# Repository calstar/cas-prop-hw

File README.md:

View this project on [CADLAB.io](https://cadlab.io/project/23051).

# cas-prop-hw
Common Avionics Stack - Prop Module - Hardware

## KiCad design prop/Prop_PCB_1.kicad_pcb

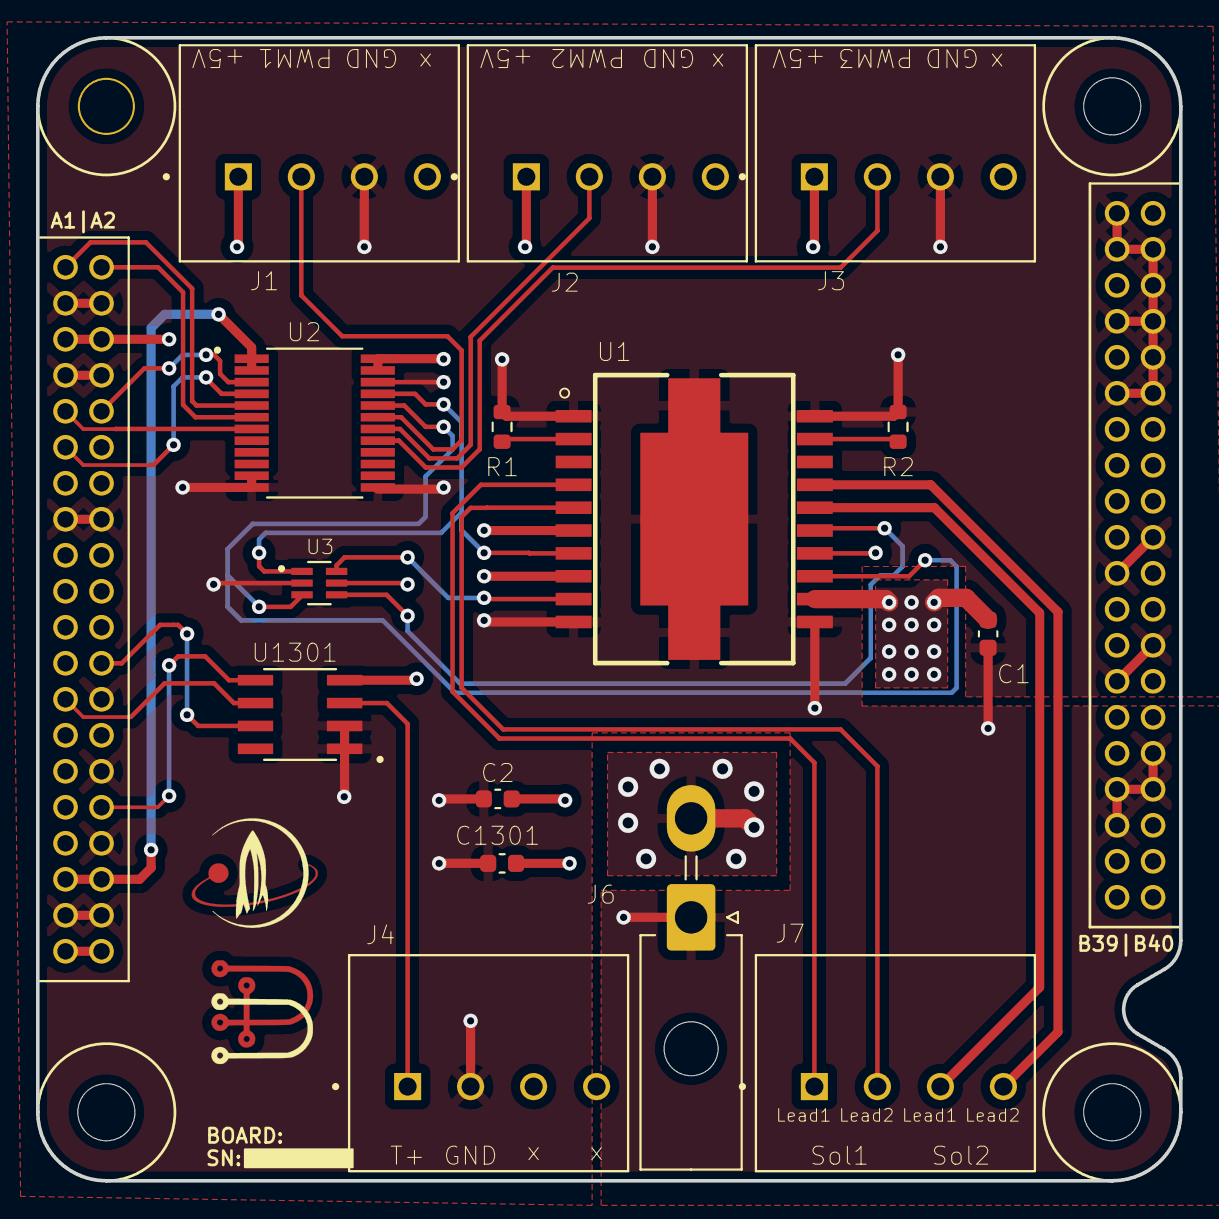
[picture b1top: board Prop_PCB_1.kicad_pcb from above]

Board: 4 copper layers, 63.5 x 63.5 mm, 18 parts (0 on the bottom side), 27 nets.

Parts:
C1, C2: 100n; C_0603_1608Metric
C1301: 0.1u; C_0603_1608Metric
J1, J2, J3, J4, J7: 1984989; PHOENIX_1984989
J5: CAS_stacking; CAS_physical
J6: Conn_01x02; Molex_Mini-Fit_Jr_5569-02A2_2x01_P4.20mm_Horizontal
R1, R2: 20; R_0603_1608Metric
Ref**: Val**; star_fancy
Ref**#2: Val**; bac
U1: L298P; SOIC127P1420X360-20N
U2: SN74LVC8T245DBR; SN74LVC8T245DBR_SOP65P780X200-24N
U3: SN74LVC2GU04DCKR; SN74LVC2GU04_SOT65P210X110-6N
U1301: MAX6675ISA+; SOIC127P600X175-8N

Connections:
+3V3: J5.A35 (3.3VA), J5.A36 (3.3VB), U2.1 (VCCA), U2.2 (DIR)
+5V: C2.2, C1301.1, J1.1, J2.1, J3.1, J5.A5 (5VA), J5.A6 (5VB), U1.6 (Vs), U1.8 (EnA), U1.14 (EnB), U2.23 (VCCB), U2.24 (VCCB), U3.5 (VCC), U1301.4 (VCC)
+24V: C1.1, J6.2, U1.12 (Vss)
+BATT: J5.A39 (VDD_BATTA), J5.A40 (VDD_BATTB)
/MAX6675ISA/T+: J4.1, U1301.3 (T+)
CS4: J5.A25 (SPI0_nSS4), U1301.6 (~CS)
GND: C1.2, C2.1, C1301.2, J1.3, J2.3, J3.3, J4.2, J5.A3 (GND1), J5.A4 (GND2), J5.A7 (GND3), J5.A8 (GND4), J5.A15 (GND5), J5.A16 (GND6), J5.A26 (GND7), J5.A30 (GND8), J5.A34 (GND9), J5.A37 (GND10), J5.A38 (GND11), J5.B1 (GND12), J5.B3 (GND13), J5.B4 (GND14), J5.B6 (GND15), J5.B7 (GND16), J5.B8 (GND17), J5.B10 (GND18), J5.B11 (GND19), J5.B12 (GND20), J5.B20 (GND22), J5.B21 (GND23), J5.B26 (GND24), J5.B27 (GND25), J5.B32 (GND26), J5.B33 (GND27), J5.B34 (GND28), J5.B35 (GND29), J6.1, R1.1, R2.2, U1.1 (GND), U1.10 (GND), U1.11 (GND), U1.20 (GND), U1.21, U1.22, U1.23, U2.11 (GND), U2.12 (GND), U2.13 (GND), U2.22 (OE), U3.2 (GND), U1301.1 (GND), U1301.2 (T-)
unnamed: R1.2, U1.2 (SENSE_A)
unnamed: R2.1, U1.19 (SENSE_B)
PWM1: J1.2, U2.19 (B3)
PWM1_33: J5.A1 (INT1), U2.5 (A3)
PWM2: J2.2, U2.18 (B4)
PWM2_33: J5.A2 (INT2), U2.6 (A4)
PWM3: J3.2, U2.17 (B5)
PWM3_33: J5.A9 (INT3), U2.7 (A5)
SPI0_MISO: J5.A24 (SPI0_MISO), U1301.7 (SO)
SPI0_SCK: J5.A32 (SPI0_SCK), U1301.5 (SCK)
Sol1: U1.7 (IN1), U2.21 (B1), U3.1 (1A)
Sol1': U1.9 (IN2), U3.6 (1Y)
Sol1Lead1: J7.1, U1.4 (OUT1)
Sol1Lead2: J7.2, U1.5 (OUT2)
Sol1_33: J5.A10 (INT4), U2.3 (A1)
Sol2: U1.13 (IN3), U2.20 (B2), U3.3 (2A)
Sol2': U1.15 (IN4), U3.4 (2Y)
Sol2Lead1: J7.3, U1.16 (OUT3)
Sol2Lead2: J7.4, U1.17 (OUT4)
Sol2_33: J5.A11 (INT5), U2.4 (A2)

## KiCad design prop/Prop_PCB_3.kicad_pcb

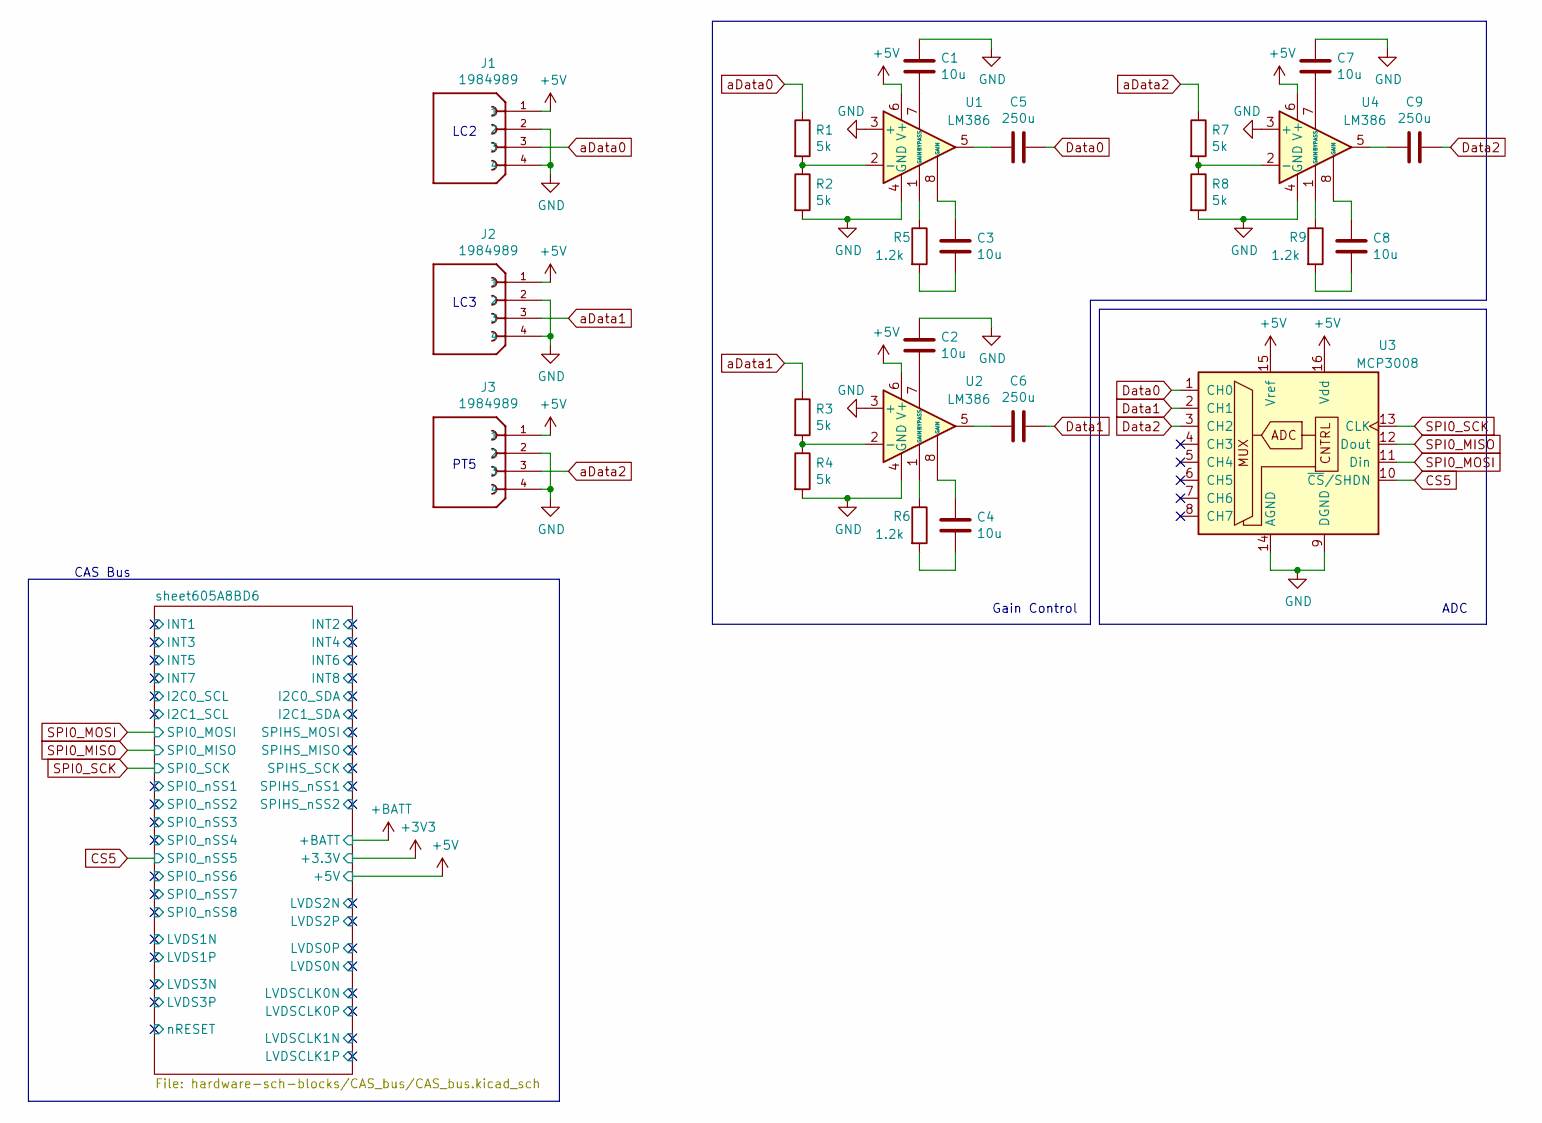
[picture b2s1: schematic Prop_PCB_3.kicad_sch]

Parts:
C1, C2, C3, C4, C7, C8: 10u; C_0603_1608Metric
C5, C6, C9: 250u; C_0603_1608Metric
J1, J2, J3: 1984989; PHOENIX_1984989; PARTREV 2018-11-03
R1, R2, R3, R4, R7, R8: 5k; R_0603_1608Metric
R5, R6, R9: 1.2k; R_0603_1608Metric
U1, U2, U4: LM386; SOIC-8_3.9x4.9mm_P1.27mm
U3: MCP3008; SOIC-16_3.9x9.9mm_P1.27mm

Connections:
+5V: J1.1, J2.1, J3.1, U1.6 (V+), U2.6 (V+), U3.15 (Vref), U3.16 (Vdd), U4.6 (V+); also elsewhere on the board
CS5: U3.10 (~CS/SHDN); also elsewhere on the board
Data0: C5.1, U3.1 (CH0)
Data1: C6.1, U3.2 (CH1)
Data2: C9.1, U3.3 (CH2)
GND: C1.1, C2.1, C7.1, J1.2, J1.4, J2.2, J2.4, J3.2, J3.4, R2.2, R4.2, R8.2, U1.3 (+), U1.4 (GND), U2.3 (+), U2.4 (GND), U3.9 (DGND), U3.14 (AGND), U4.3 (+), U4.4 (GND); also elsewhere on the board
unnamed: C1.2, U1.7 (BYPASS)
unnamed: C2.2, U2.7 (BYPASS)
unnamed: C3.1, U1.8 (GAIN)
unnamed: C3.2, R5.2
unnamed: C4.1, U2.8 (GAIN)
unnamed: C4.2, R6.2
unnamed: C5.2, U1.5
unnamed: C6.2, U2.5
unnamed: C7.2, U4.7 (BYPASS)
unnamed: C8.1, U4.8 (GAIN)
unnamed: C8.2, R9.2
unnamed: C9.2, U4.5
unnamed: R1.2, R2.1, U1.2 (-)
unnamed: R3.2, R4.1, U2.2 (-)
unnamed: R5.1, U1.1 (GAIN)
unnamed: R6.1, U2.1 (GAIN)
unnamed: R7.2, R8.1, U4.2 (-)
unnamed: R9.1, U4.1 (GAIN)
SPI0_MISO: U3.12 (Dout); also elsewhere on the board
SPI0_MOSI: U3.11 (Din); also elsewhere on the board
SPI0_SCK: U3.13 (CLK); also elsewhere on the board
aData0: J1.3, R1.1
aData1: J2.3, R3.1
aData2: J3.3, R7.1

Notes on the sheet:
CAS Bus
LC2
Gain Control
ADC
PT5
LC3

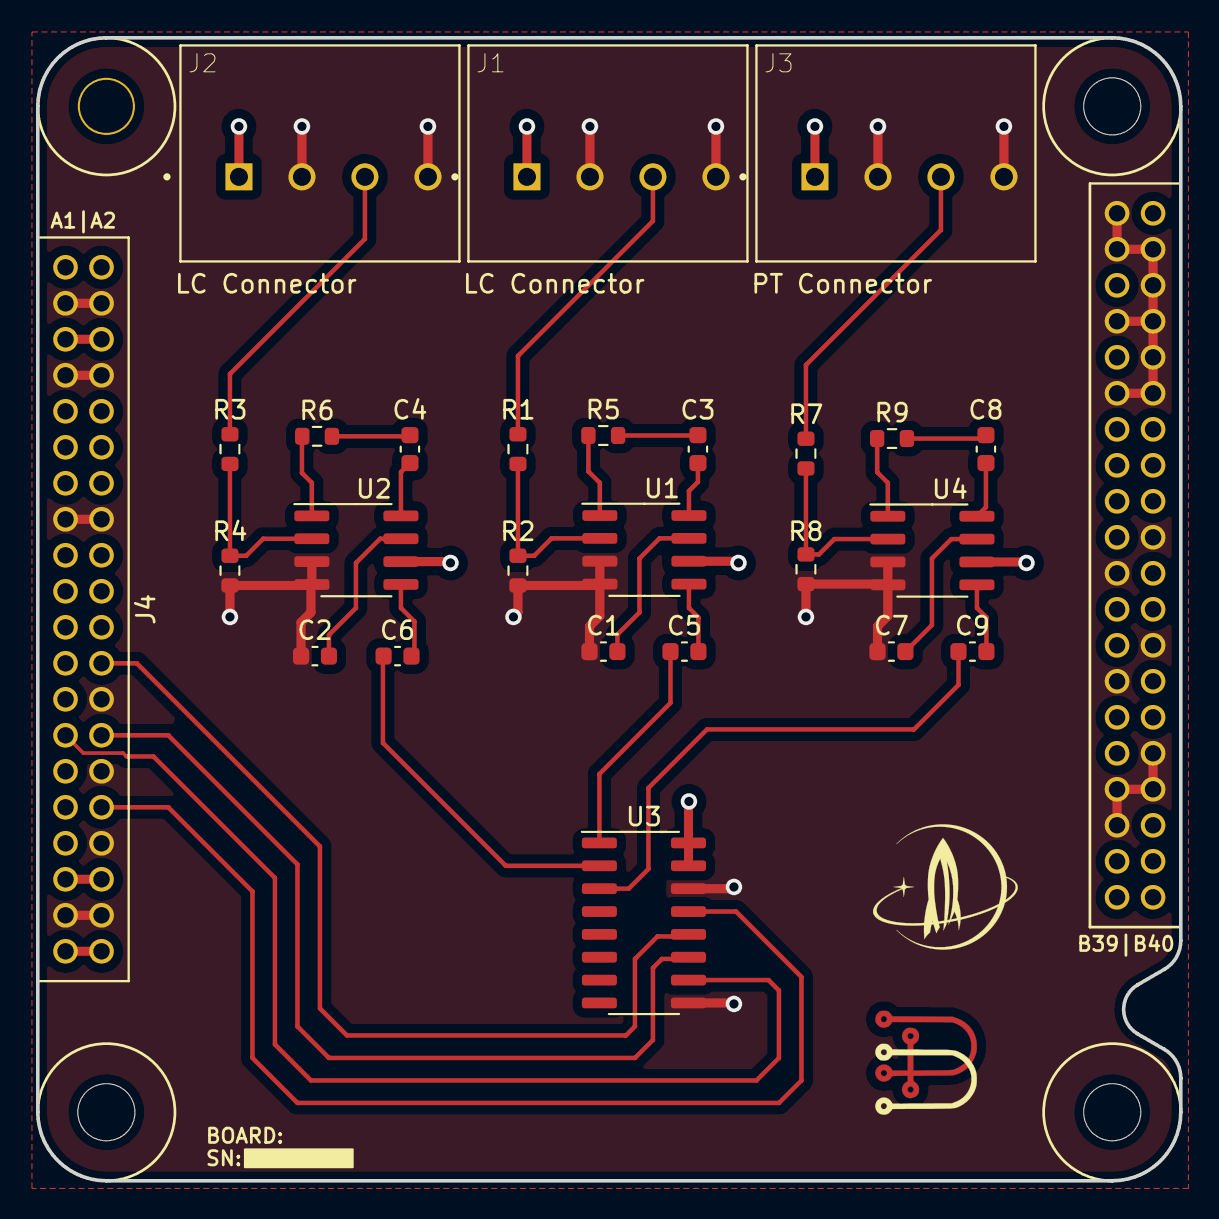
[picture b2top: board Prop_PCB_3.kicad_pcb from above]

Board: 4 copper layers, 63.5 x 63.5 mm, 27 parts (0 on the bottom side), 32 nets.

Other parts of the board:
J4: CAS_stacking; CAS_physical
Ref**: Val**; bac

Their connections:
+3V3: J4.A35 (3.3VA), J4.A36 (3.3VB)
+5V: J4.A5 (5VA), J4.A6 (5VB); also elsewhere on the board
+BATT: J4.A39 (VDD_BATTA), J4.A40 (VDD_BATTB)
CS5: J4.A27 (SPI0_nSS5); also elsewhere on the board
GND: J4.A3 (GND1), J4.A4 (GND2), J4.A7 (GND3), J4.A8 (GND4), J4.A15 (GND5), J4.A16 (GND6), J4.A26 (GND7), J4.A30 (GND8), J4.A34 (GND9), J4.A37 (GND10), J4.A38 (GND11), J4.B1 (GND12), J4.B3 (GND13), J4.B4 (GND14), J4.B6 (GND15), J4.B7 (GND16), J4.B8 (GND17), J4.B10 (GND18), J4.B11 (GND19), J4.B12 (GND20), J4.B20 (GND22), J4.B21 (GND23), J4.B26 (GND24), J4.B27 (GND25), J4.B32 (GND26), J4.B33 (GND27), J4.B34 (GND28), J4.B35 (GND29); also elsewhere on the board
SPI0_MISO: J4.A24 (SPI0_MISO); also elsewhere on the board
SPI0_MOSI: J4.A28 (SPI0_MOSI); also elsewhere on the board
SPI0_SCK: J4.A32 (SPI0_SCK); also elsewhere on the board

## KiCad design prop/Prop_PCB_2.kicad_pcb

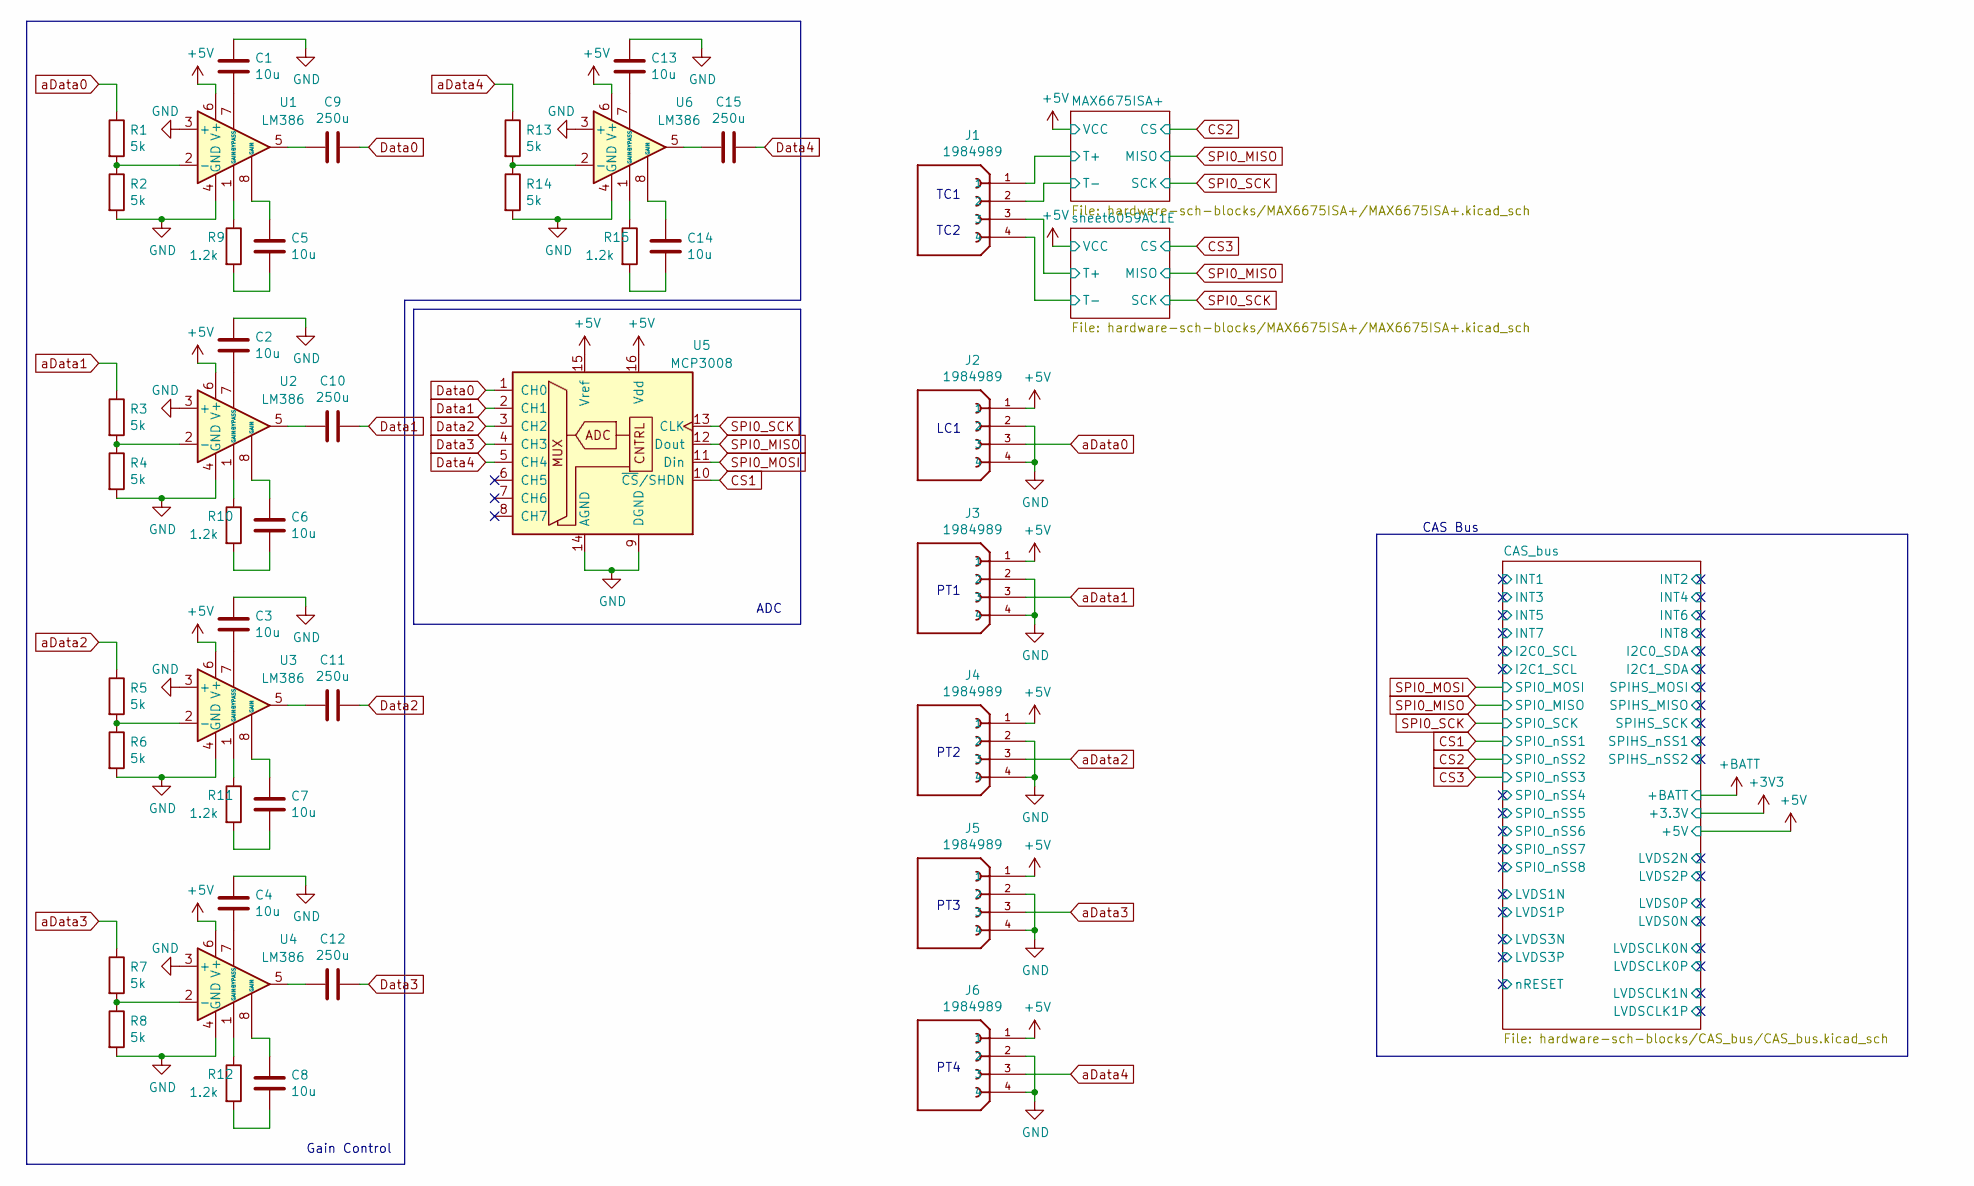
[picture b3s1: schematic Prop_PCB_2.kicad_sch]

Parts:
C1, C2, C3, C4, C5, C6, C7, C8, C13, C14: 10u; C_0603_1608Metric
C9, C10, C11, C12, C15: 250u; C_0603_1608Metric
J1, J2, J3, J4, J5, J6: 1984989; PHOENIX_1984989; PARTREV 2018-11-03
R1, R2, R3, R4, R5, R6, R7, R8, R13, R14: 5k; R_0603_1608Metric
R9, R10, R11, R12, R15: 1.2k; R_0603_1608Metric
U1, U2, U3, U4, U6: LM386; SOIC-8_3.9x4.9mm_P1.27mm
U5: MCP3008; SOIC-16_3.9x9.9mm_P1.27mm

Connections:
+5V: J2.1, J3.1, J4.1, J5.1, J6.1, U1.6 (V+), U2.6 (V+), U3.6 (V+), U4.6 (V+), U5.15 (Vref), U5.16 (Vdd), U6.6 (V+); also elsewhere on the board
/MAX6675ISA+/T+: J1.1; also elsewhere on the board
/sheet6059AC1E/T+: J1.3; also elsewhere on the board
CS1: U5.10 (~CS/SHDN); also elsewhere on the board
Data0: C9.1, U5.1 (CH0)
Data1: C10.1, U5.2 (CH1)
Data2: C11.1, U5.3 (CH2)
Data3: C12.1, U5.4 (CH3)
Data4: C15.1, U5.5 (CH4)
GND: C1.1, C2.1, C3.1, C4.1, C13.1, J1.2, J1.4, J2.2, J2.4, J3.2, J3.4, J4.2, J4.4, J5.2, J5.4, J6.2, J6.4, R2.2, R4.2, R6.2, R8.2, R14.2, U1.3 (+), U1.4 (GND), U2.3 (+), U2.4 (GND), U3.3 (+), U3.4 (GND), U4.3 (+), U4.4 (GND), U5.9 (DGND), U5.14 (AGND), U6.3 (+), U6.4 (GND); also elsewhere on the board
unnamed: C1.2, U1.7 (BYPASS)
unnamed: C2.2, U2.7 (BYPASS)
unnamed: C3.2, U3.7 (BYPASS)
unnamed: C4.2, U4.7 (BYPASS)
unnamed: C5.1, U1.8 (GAIN)
unnamed: C5.2, R9.2
unnamed: C6.1, U2.8 (GAIN)
unnamed: C6.2, R10.2
unnamed: C7.1, U3.8 (GAIN)
unnamed: C7.2, R11.2
unnamed: C8.1, U4.8 (GAIN)
unnamed: C8.2, R12.2
unnamed: C9.2, U1.5
unnamed: C10.2, U2.5
unnamed: C11.2, U3.5
unnamed: C12.2, U4.5
unnamed: C13.2, U6.7 (BYPASS)
unnamed: C14.1, U6.8 (GAIN)
unnamed: C14.2, R15.2
unnamed: C15.2, U6.5
unnamed: R1.2, R2.1, U1.2 (-)
unnamed: R3.2, R4.1, U2.2 (-)
unnamed: R5.2, R6.1, U3.2 (-)
unnamed: R7.2, R8.1, U4.2 (-)
unnamed: R9.1, U1.1 (GAIN)
unnamed: R10.1, U2.1 (GAIN)
unnamed: R11.1, U3.1 (GAIN)
unnamed: R12.1, U4.1 (GAIN)
unnamed: R13.2, R14.1, U6.2 (-)
unnamed: R15.1, U6.1 (GAIN)
SPI0_MISO: U5.12 (Dout); also elsewhere on the board
SPI0_MOSI: U5.11 (Din); also elsewhere on the board
SPI0_SCK: U5.13 (CLK); also elsewhere on the board
aData0: J2.3, R1.1
aData1: J3.3, R3.1
aData2: J4.3, R5.1
aData3: J5.3, R7.1
aData4: J6.3, R13.1

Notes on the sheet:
Gain Control
PT3
PT2
CAS Bus
PT4
LC1
PT1
TC1
ADC
TC2

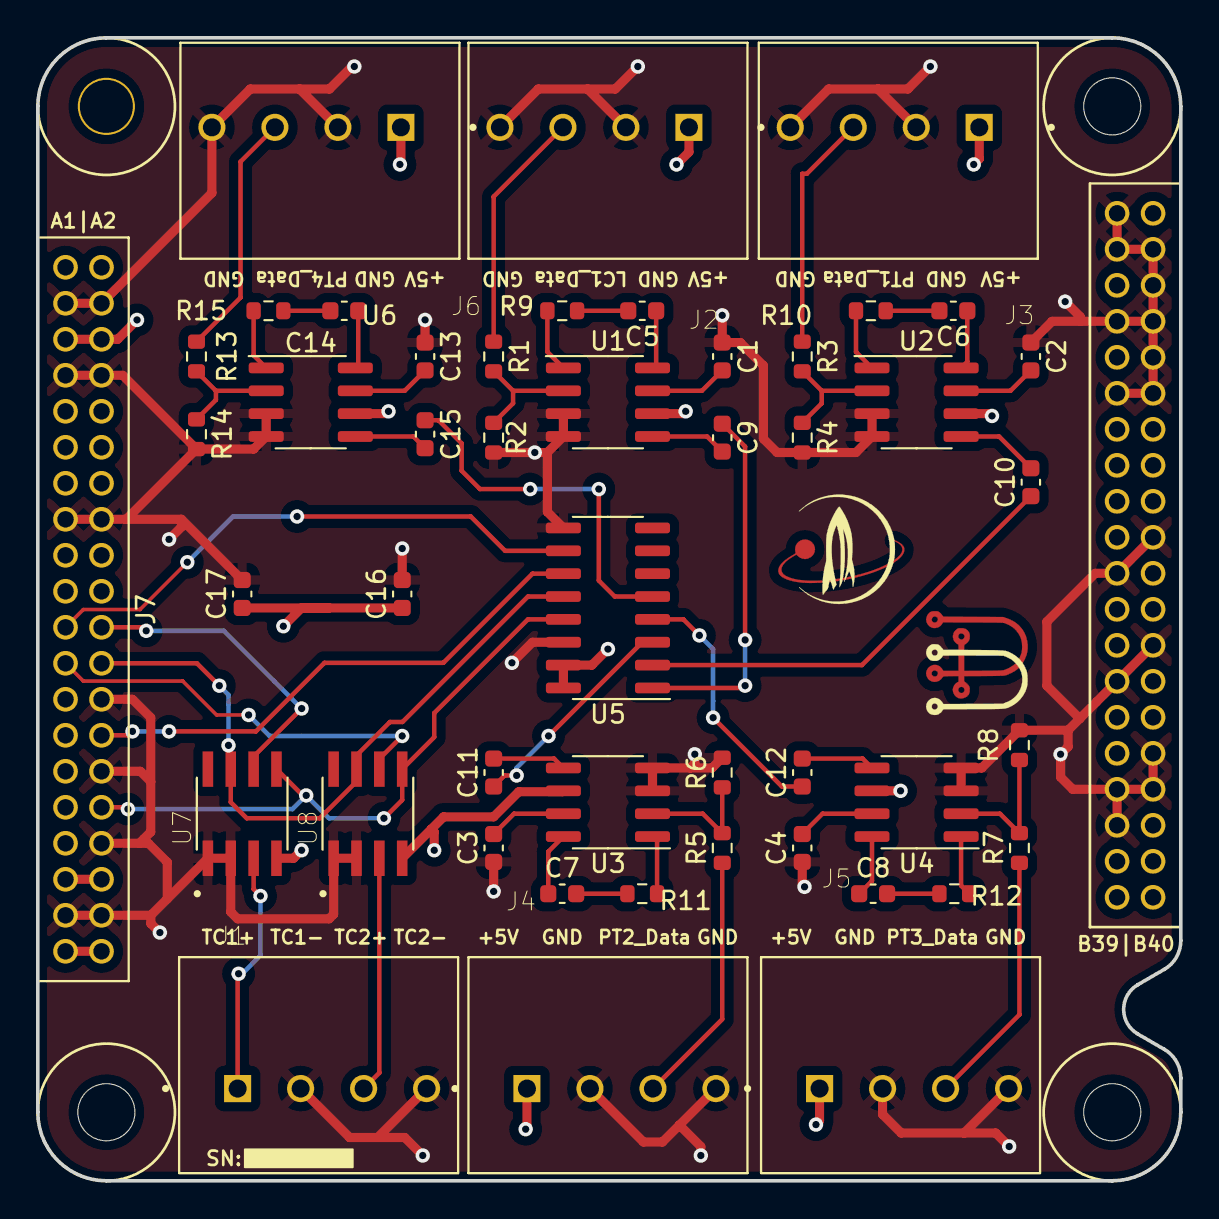
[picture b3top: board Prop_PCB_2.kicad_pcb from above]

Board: 4 copper layers, 63.5 x 63.5 mm, 49 parts (0 on the bottom side), 52 nets.

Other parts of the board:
C16, C17: 0.1u; C_0603_1608Metric
J7: CAS_stacking; CAS_physical
Ref**: Val**; star_fancy
Ref**#2: Val**; bac
U7, U8: MAX6675ISA+; SOIC127P600X175-8N

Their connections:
+3V3: J7.A35 (3.3VA), J7.A36 (3.3VB)
+5V: C16.1, C17.1, J7.A5 (5VA), J7.A6 (5VB), U7.4 (VCC), U8.4 (VCC); also elsewhere on the board
+BATT: J7.A39 (VDD_BATTA), J7.A40 (VDD_BATTB)
/MAX6675ISA+/T+: U7.3 (T+); also elsewhere on the board
/sheet6059AC1E/T+: U8.3 (T+); also elsewhere on the board
CS1: J7.A21 (SPI0_nSS1); also elsewhere on the board
CS2: J7.A22 (SPI0_nSS2), U7.6 (~CS)
CS3: J7.A23 (SPI0_nSS3), U8.6 (~CS)
GND: C16.2, C17.2, J7.A3 (GND1), J7.A4 (GND2), J7.A7 (GND3), J7.A8 (GND4), J7.A15 (GND5), J7.A16 (GND6), J7.A26 (GND7), J7.A30 (GND8), J7.A34 (GND9), J7.A37 (GND10), J7.A38 (GND11), J7.B1 (GND12), J7.B3 (GND13), J7.B4 (GND14), J7.B6 (GND15), J7.B7 (GND16), J7.B8 (GND17), J7.B10 (GND18), J7.B11 (GND19), J7.B12 (GND20), J7.B20 (GND22), J7.B21 (GND23), J7.B26 (GND24), J7.B27 (GND25), J7.B32 (GND26), J7.B33 (GND27), J7.B34 (GND28), J7.B35 (GND29), U7.1 (GND), U7.2 (T-), U8.1 (GND), U8.2 (T-); also elsewhere on the board
SPI0_MISO: J7.A24 (SPI0_MISO), U7.7 (SO), U8.7 (SO); also elsewhere on the board
SPI0_MOSI: J7.A28 (SPI0_MOSI); also elsewhere on the board
SPI0_SCK: J7.A32 (SPI0_SCK), U7.5 (SCK), U8.5 (SCK); also elsewhere on the board

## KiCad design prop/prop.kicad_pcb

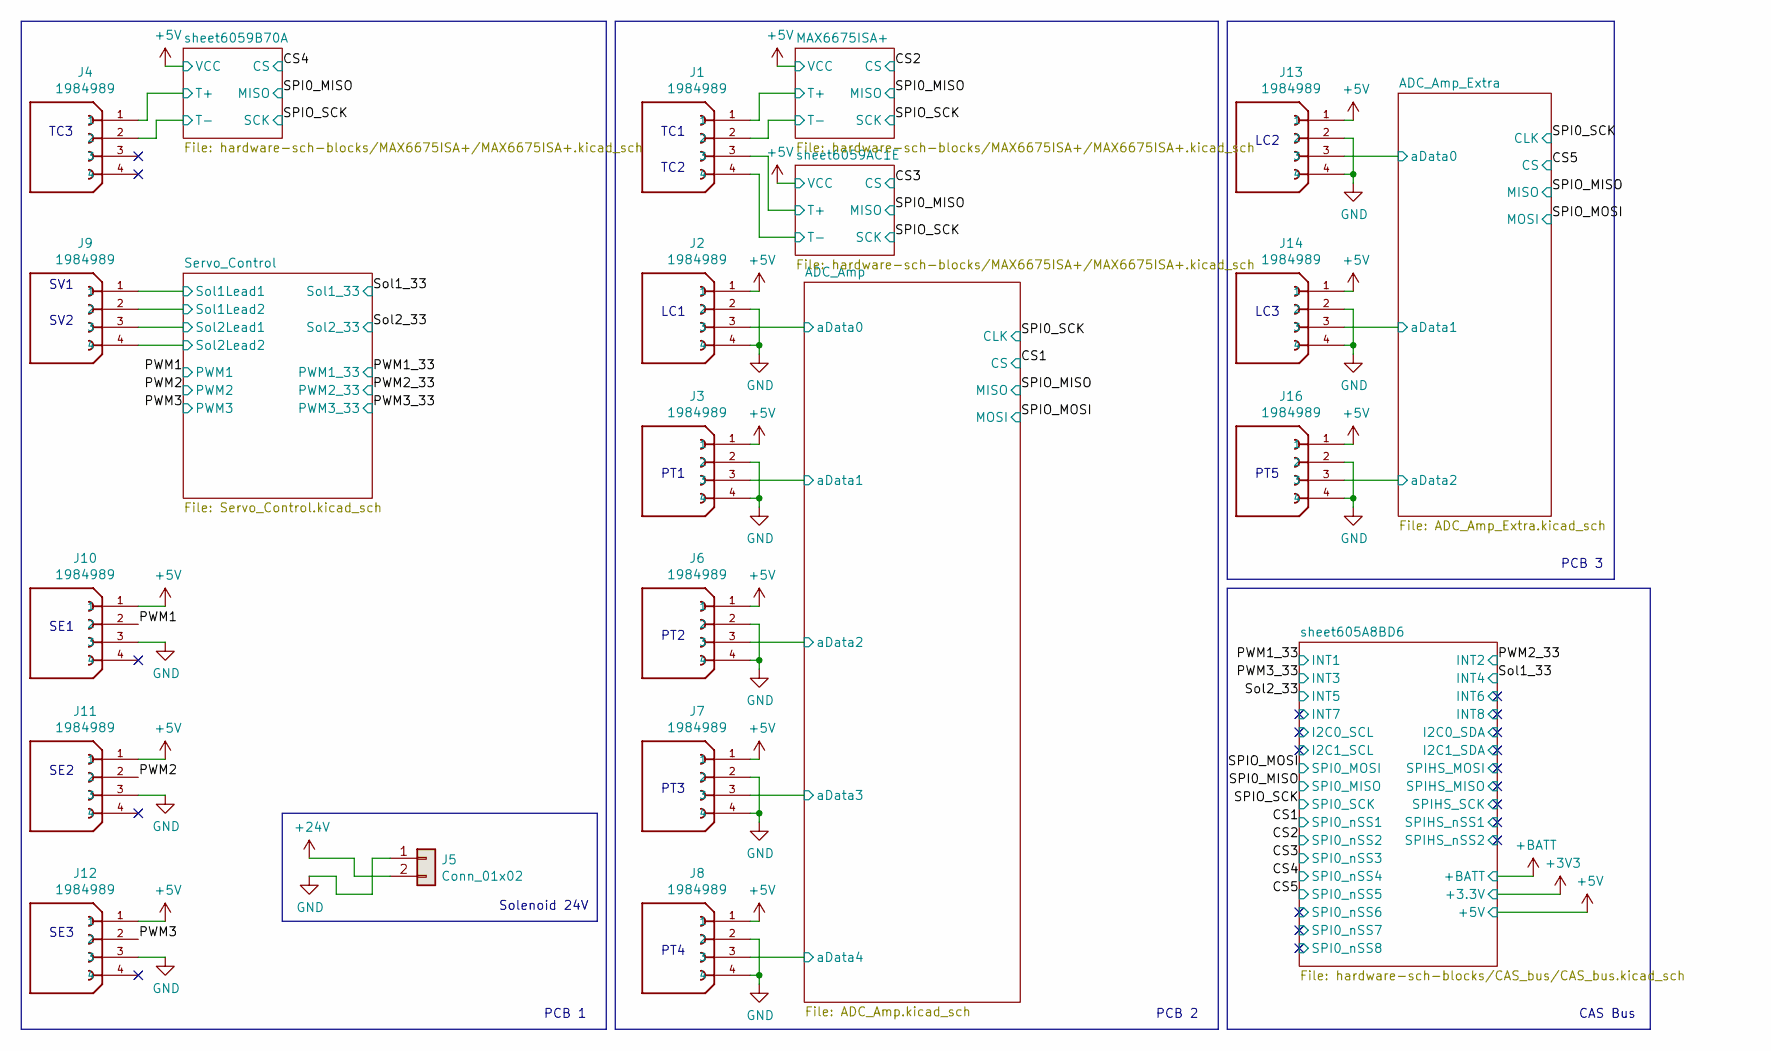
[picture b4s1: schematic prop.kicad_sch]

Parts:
J1, J2, J3, J4, J6, J7, J8, J9, J10, J11, J12, J13, J14, J16: 1984989; PHOENIX_1984989; PARTREV 2018-11-03
J5: Conn_01x02; Molex_Mini-Fit_Jr_5569-02A2_2x01_P4.20mm_Horizontal

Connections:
+5V: J2.1, J3.1, J6.1, J7.1, J8.1, J10.1, J11.1, J12.1, J13.1, J14.1, J16.1; also elsewhere on the board
+24V: J5.2; also elsewhere on the board
/ADC_Amp/aData0: J2.3; also elsewhere on the board
/ADC_Amp/aData1: J3.3; also elsewhere on the board
/ADC_Amp/aData2: J6.3; also elsewhere on the board
/ADC_Amp/aData3: J7.3; also elsewhere on the board
/ADC_Amp/aData4: J8.3; also elsewhere on the board
/ADC_Amp_Extra/aData0: J13.3; also elsewhere on the board
/ADC_Amp_Extra/aData1: J14.3; also elsewhere on the board
/ADC_Amp_Extra/aData2: J16.3; also elsewhere on the board
/MAX6675ISA+/T+: J1.1; also elsewhere on the board
/PWM1: J10.2; also elsewhere on the board
/PWM2: J11.2; also elsewhere on the board
/PWM3: J12.2; also elsewhere on the board
/Servo_Control/Sol1Lead1: J9.1; also elsewhere on the board
/Servo_Control/Sol1Lead2: J9.2; also elsewhere on the board
/Servo_Control/Sol2Lead1: J9.3; also elsewhere on the board
/Servo_Control/Sol2Lead2: J9.4; also elsewhere on the board
/sheet6059AC1E/T+: J1.3; also elsewhere on the board
/sheet6059B70A/T+: J4.1; also elsewhere on the board
GND: J1.2, J1.4, J2.2, J2.4, J3.2, J3.4, J4.2, J5.1, J6.2, J6.4, J7.2, J7.4, J8.2, J8.4, J10.3, J11.3, J12.3, J13.2, J13.4, J14.2, J14.4, J16.2, J16.4; also elsewhere on the board

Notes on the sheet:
PCB 2
TC2
PCB 3
SV2
SE2
SV1
PT4
PCB 1
PT1
PT3
PT2
TC1
PT5
LC3
SE1
Solenoid 24V
LC2
SE3
CAS Bus
LC1
TC3

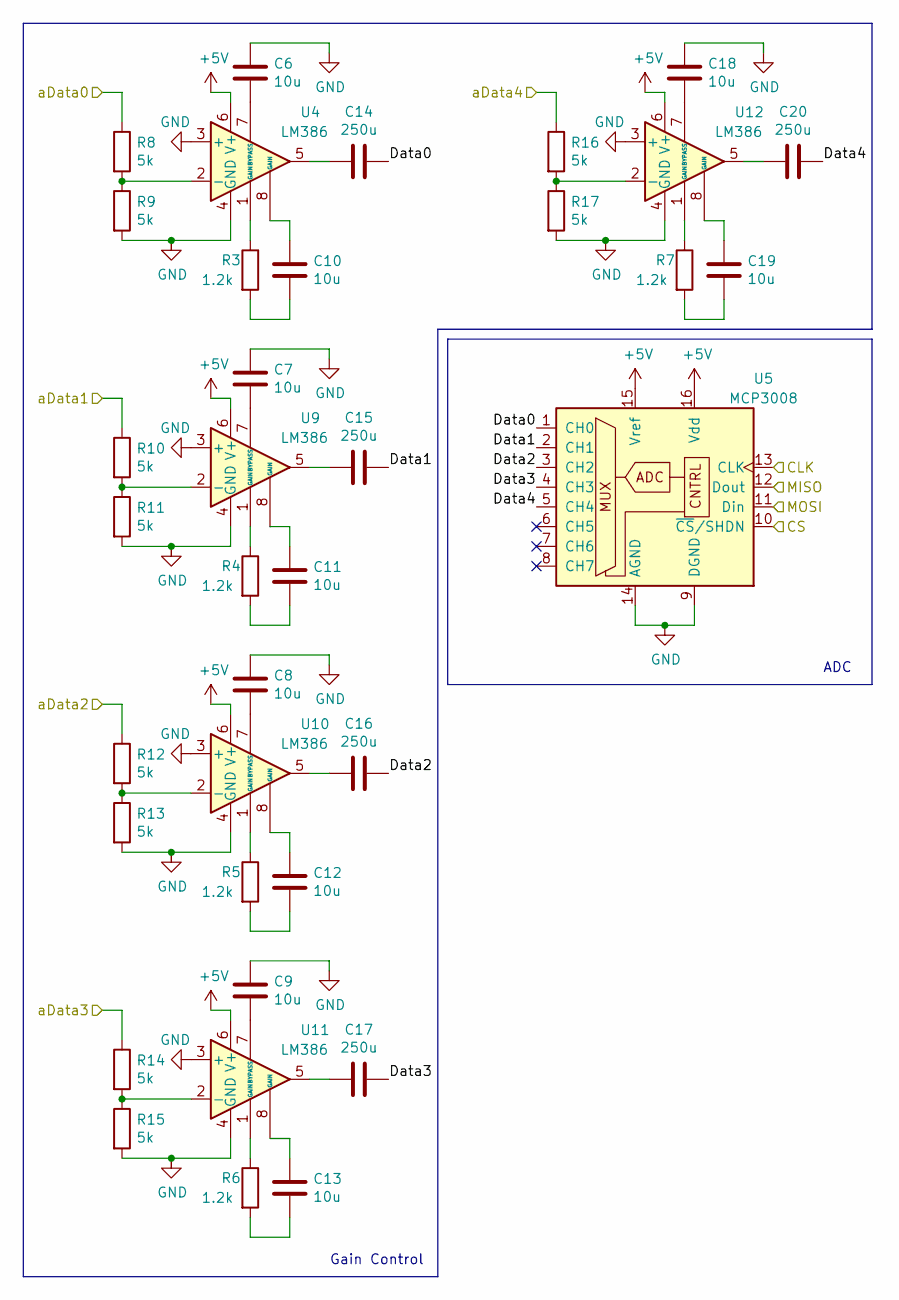
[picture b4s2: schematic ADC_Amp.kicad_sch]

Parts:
C6, C7, C8, C9, C10, C11, C12, C13, C18, C19: 10u; C_0603_1608Metric
C14, C15, C16, C17, C20: 250u; C_0603_1608Metric
R3, R4, R5, R6, R7: 1.2k; R_0603_1608Metric
R8, R9, R10, R11, R12, R13, R14, R15, R16, R17: 5k; R_0603_1608Metric
U4, U9, U10, U11, U12: LM386; SOIC-8_3.9x4.9mm_P1.27mm
U5: MCP3008; SOIC-16_3.9x9.9mm_P1.27mm

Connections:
+5V: U4.6 (V+), U5.15 (Vref), U5.16 (Vdd), U9.6 (V+), U10.6 (V+), U11.6 (V+), U12.6 (V+); also elsewhere on the board
/ADC_Amp/Data0: C14.1, U5.1 (CH0)
/ADC_Amp/Data1: C15.1, U5.2 (CH1)
/ADC_Amp/Data2: C16.1, U5.3 (CH2)
/ADC_Amp/Data3: C17.1, U5.4 (CH3)
/ADC_Amp/Data4: C20.1, U5.5 (CH4)
/ADC_Amp/aData0: R8.1; also elsewhere on the board
/ADC_Amp/aData1: R10.1; also elsewhere on the board
/ADC_Amp/aData2: R12.1; also elsewhere on the board
/ADC_Amp/aData3: R14.1; also elsewhere on the board
/ADC_Amp/aData4: R16.1; also elsewhere on the board
/CS1: U5.10 (~CS/SHDN); also elsewhere on the board
/SPI0_SCK: U5.13 (CLK); also elsewhere on the board
/SPIO_MISO: U5.12 (Dout); also elsewhere on the board
/SPIO_MOSI: U5.11 (Din); also elsewhere on the board
GND: C6.1, C7.1, C8.1, C9.1, C18.1, R9.2, R11.2, R13.2, R15.2, R17.2, U4.3 (+), U4.4 (GND), U5.9 (DGND), U5.14 (AGND), U9.3 (+), U9.4 (GND), U10.3 (+), U10.4 (GND), U11.3 (+), U11.4 (GND), U12.3 (+), U12.4 (GND); also elsewhere on the board
unnamed: C6.2, U4.7 (BYPASS)
unnamed: C7.2, U9.7 (BYPASS)
unnamed: C8.2, U10.7 (BYPASS)
unnamed: C9.2, U11.7 (BYPASS)
unnamed: C10.1, U4.8 (GAIN)
unnamed: C10.2, R3.2
unnamed: C11.1, U9.8 (GAIN)
unnamed: C11.2, R4.2
unnamed: C12.1, U10.8 (GAIN)
unnamed: C12.2, R5.2
unnamed: C13.1, U11.8 (GAIN)
unnamed: C13.2, R6.2
unnamed: C14.2, U4.5
unnamed: C15.2, U9.5
unnamed: C16.2, U10.5
unnamed: C17.2, U11.5
unnamed: C18.2, U12.7 (BYPASS)
unnamed: C19.1, U12.8 (GAIN)
unnamed: C19.2, R7.2
unnamed: C20.2, U12.5
unnamed: R3.1, U4.1 (GAIN)
unnamed: R4.1, U9.1 (GAIN)
unnamed: R5.1, U10.1 (GAIN)
unnamed: R6.1, U11.1 (GAIN)
unnamed: R7.1, U12.1 (GAIN)
unnamed: R8.2, R9.1, U4.2 (-)
unnamed: R10.2, R11.1, U9.2 (-)
unnamed: R12.2, R13.1, U10.2 (-)
unnamed: R14.2, R15.1, U11.2 (-)
unnamed: R16.2, R17.1, U12.2 (-)

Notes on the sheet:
Gain Control
ADC

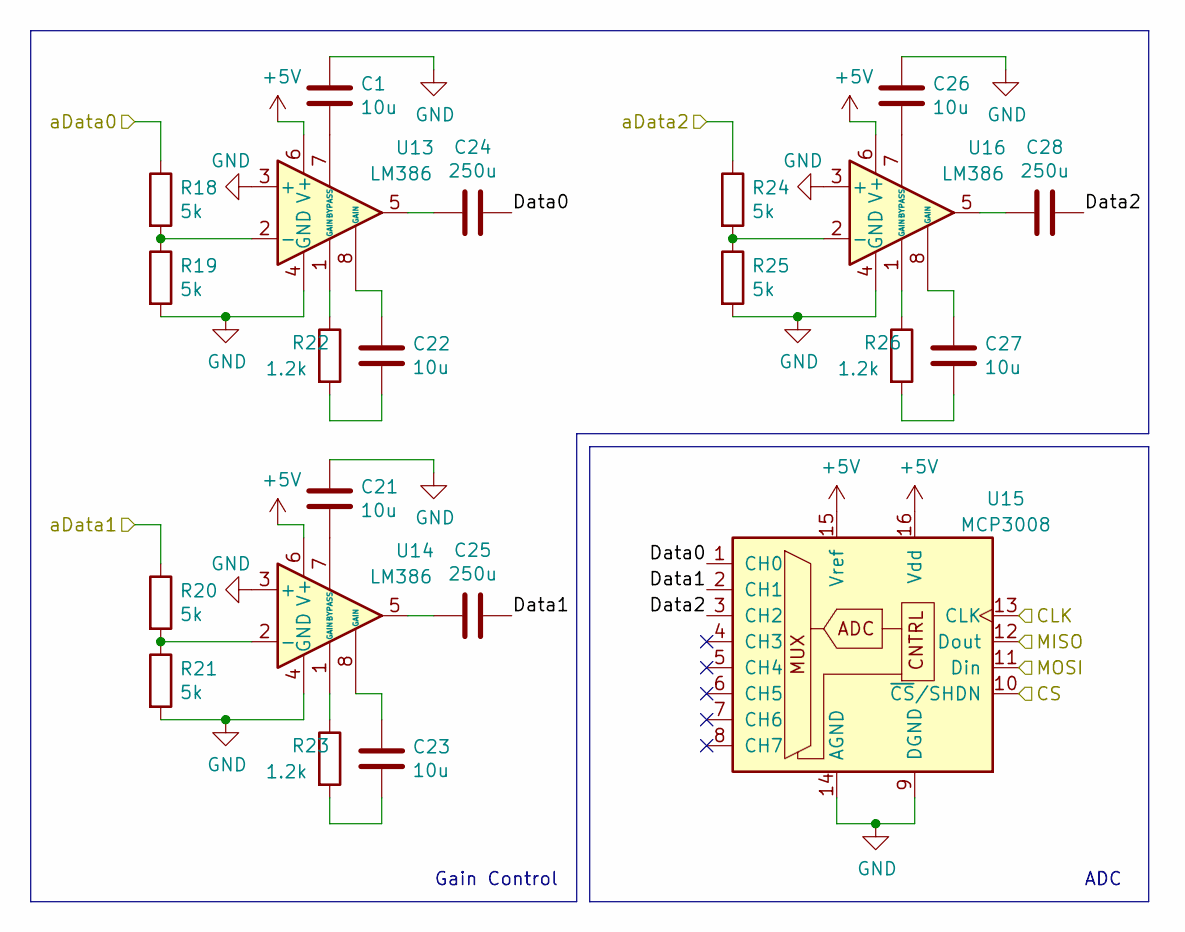
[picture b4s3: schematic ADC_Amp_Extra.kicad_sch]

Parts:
C1, C21, C22, C23, C26, C27: 10u; C_0603_1608Metric
C24, C25, C28: 250u; C_0603_1608Metric
R18, R19, R20, R21, R24, R25: 5k; R_0603_1608Metric
R22, R23, R26: 1.2k; R_0603_1608Metric
U13, U14, U16: LM386; SOIC-8_3.9x4.9mm_P1.27mm
U15: MCP3008; SOIC-16_3.9x9.9mm_P1.27mm

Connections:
+5V: U13.6 (V+), U14.6 (V+), U15.15 (Vref), U15.16 (Vdd), U16.6 (V+); also elsewhere on the board
/ADC_Amp_Extra/Data0: C24.1, U15.1 (CH0)
/ADC_Amp_Extra/Data1: C25.1, U15.2 (CH1)
/ADC_Amp_Extra/Data2: C28.1, U15.3 (CH2)
/ADC_Amp_Extra/aData0: R18.1; also elsewhere on the board
/ADC_Amp_Extra/aData1: R20.1; also elsewhere on the board
/ADC_Amp_Extra/aData2: R24.1; also elsewhere on the board
/CS5: U15.10 (~CS/SHDN); also elsewhere on the board
/SPI0_SCK: U15.13 (CLK); also elsewhere on the board
/SPIO_MISO: U15.12 (Dout); also elsewhere on the board
/SPIO_MOSI: U15.11 (Din); also elsewhere on the board
GND: C1.1, C21.1, C26.1, R19.2, R21.2, R25.2, U13.3 (+), U13.4 (GND), U14.3 (+), U14.4 (GND), U15.9 (DGND), U15.14 (AGND), U16.3 (+), U16.4 (GND); also elsewhere on the board
unnamed: C1.2, U13.7 (BYPASS)
unnamed: C21.2, U14.7 (BYPASS)
unnamed: C22.1, U13.8 (GAIN)
unnamed: C22.2, R22.2
unnamed: C23.1, U14.8 (GAIN)
unnamed: C23.2, R23.2
unnamed: C24.2, U13.5
unnamed: C25.2, U14.5
unnamed: C26.2, U16.7 (BYPASS)
unnamed: C27.1, U16.8 (GAIN)
unnamed: C27.2, R26.2
unnamed: C28.2, U16.5
unnamed: R18.2, R19.1, U13.2 (-)
unnamed: R20.2, R21.1, U14.2 (-)
unnamed: R22.1, U13.1 (GAIN)
unnamed: R23.1, U14.1 (GAIN)
unnamed: R24.2, R25.1, U16.2 (-)
unnamed: R26.1, U16.1 (GAIN)

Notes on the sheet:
Gain Control
ADC

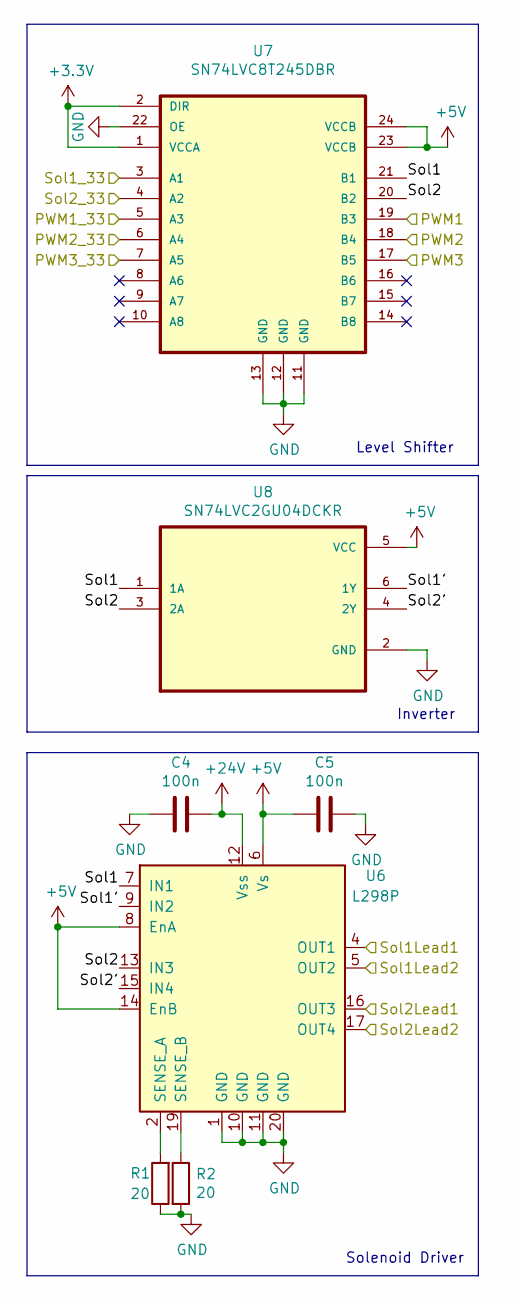
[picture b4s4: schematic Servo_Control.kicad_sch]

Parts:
C4, C5: 100n; C_0603_1608Metric
R1, R2: 20; R_0603_1608Metric
U6: L298P; SOIC127P1420X360-20N
U7: SN74LVC8T245DBR; SN74LVC8T245DBR_SOP65P780X200-24N
U8: SN74LVC2GU04DCKR; SN74LVC2GU04_SOT65P210X110-6N

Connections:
+3V3: U7.1 (VCCA), U7.2 (DIR); also elsewhere on the board
+5V: C5.2, U6.6 (Vs), U6.8 (EnA), U6.14 (EnB), U7.23 (VCCB), U7.24 (VCCB), U8.5 (VCC); also elsewhere on the board
+24V: C4.1, U6.12 (Vss); also elsewhere on the board
/PWM1: U7.19 (B3); also elsewhere on the board
/PWM1_33: U7.5 (A3); also elsewhere on the board
/PWM2: U7.18 (B4); also elsewhere on the board
/PWM2_33: U7.6 (A4); also elsewhere on the board
/PWM3: U7.17 (B5); also elsewhere on the board
/PWM3_33: U7.7 (A5); also elsewhere on the board
/Servo_Control/Sol1: U6.7 (IN1), U7.21 (B1), U8.1 (1A)
/Servo_Control/Sol1': U6.9 (IN2), U8.6 (1Y)
/Servo_Control/Sol1Lead1: U6.4 (OUT1); also elsewhere on the board
/Servo_Control/Sol1Lead2: U6.5 (OUT2); also elsewhere on the board
/Servo_Control/Sol2: U6.13 (IN3), U7.20 (B2), U8.3 (2A)
/Servo_Control/Sol2': U6.15 (IN4), U8.4 (2Y)
/Servo_Control/Sol2Lead1: U6.16 (OUT3); also elsewhere on the board
/Servo_Control/Sol2Lead2: U6.17 (OUT4); also elsewhere on the board
/Sol1_33: U7.3 (A1); also elsewhere on the board
/Sol2_33: U7.4 (A2); also elsewhere on the board
GND: C4.2, C5.1, R1.1, R2.2, U6.1 (GND), U6.10 (GND), U6.11 (GND), U6.20 (GND), U7.11 (GND), U7.12 (GND), U7.13 (GND), U7.22 (OE), U8.2 (GND); also elsewhere on the board
unnamed: R1.2, U6.2 (SENSE_A)
unnamed: R2.1, U6.19 (SENSE_B)

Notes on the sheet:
Level Shifter
Solenoid Driver
Inverter
